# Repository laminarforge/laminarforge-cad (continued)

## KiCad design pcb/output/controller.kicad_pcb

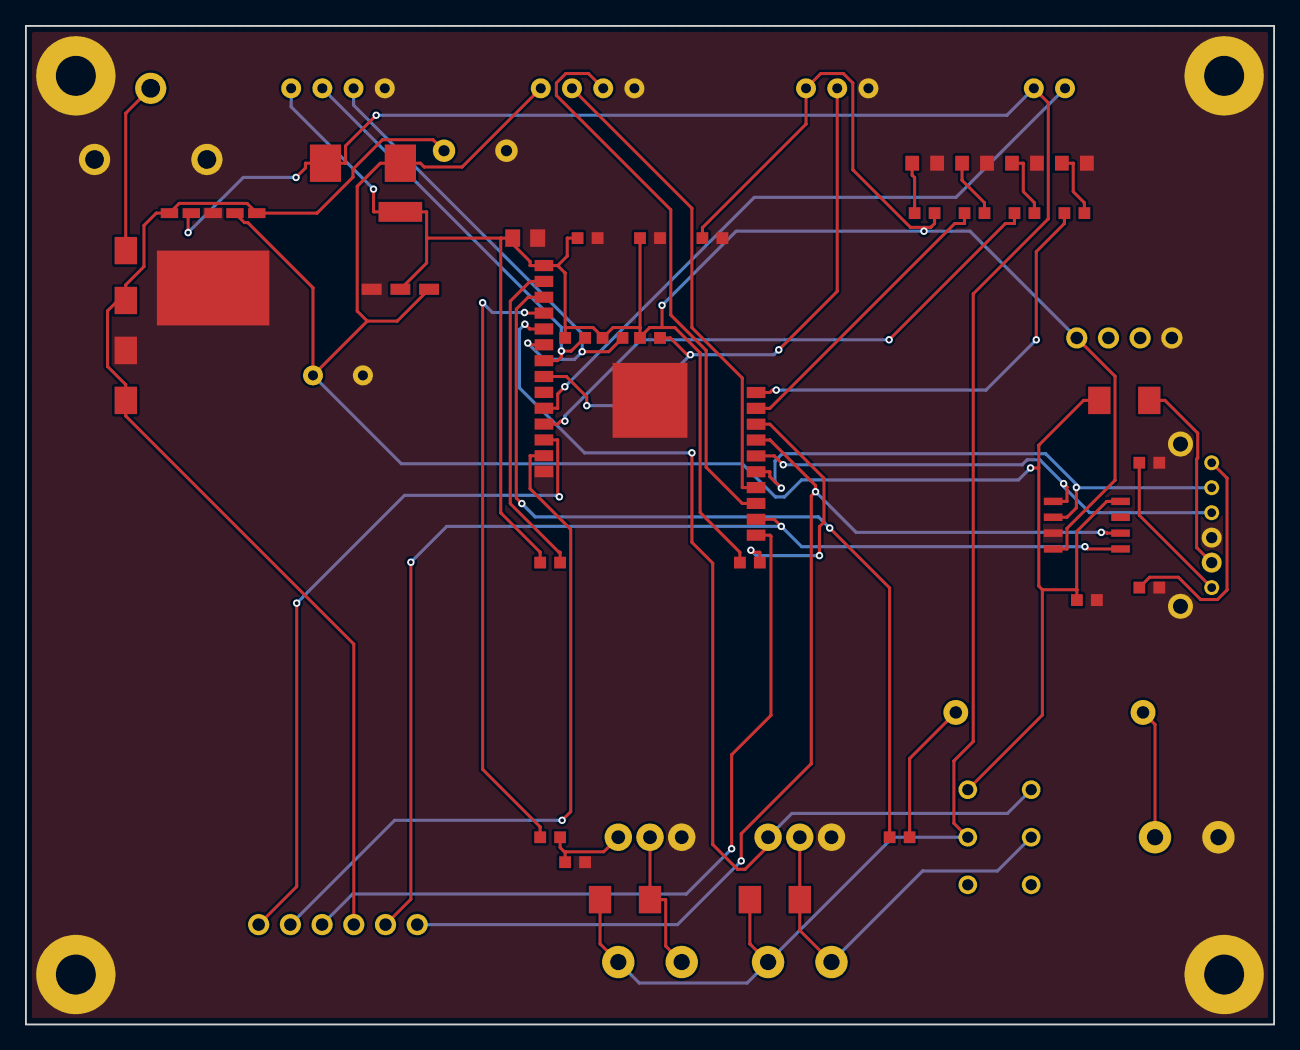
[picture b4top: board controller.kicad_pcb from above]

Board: 2 copper layers, 100.0 x 80.0 mm, 54 parts (0 on the bottom side), 39 nets.

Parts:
C1: 220uF_35V; CP_Radial_D8.0mm
C2: 220uF_10V; CP_Radial_D6.3mm
C3, C4, C5, C7: 100nF; C_0603
C6: 10uF; C_0805
D1, D3, D4, D5: SS54; SMA
D2: SMBJ30A; SMB
H1, H2, H3, H4: MountingHole_3.2mm_M3
J1: DC_BARREL_2.1x5.5mm; BarrelJack_2.1x5.5mm
J2: KSD9700_100C_NC; ThermalCutoff_KSD9700
J3: ScrewTerm_SSR_Ctrl; ScrewTerm_2.54mm_2P
J4: ScrewTerm_Fan; ScrewTerm_2.54mm_2P
J5: ScrewTerm_Solenoid; ScrewTerm_2.54mm_2P
J6: JST_SHT40; JST_PH_4P
J7: JST_MHZ19; JST_PH_4P
J8: JST_DS18B20; JST_PH_3P
J9: JST_Window_Heater; JST_PH_2P
J10: USB-C_Receptacle; USB_C_Receptacle_HRO-TYPE-C-31-M-12
J11: TMC2209_Header; PinHeader_1x6_2.54mm
J12: SWD_Header; PinHeader_1x4_2.54mm
K1: G6K-2F-Y; Relay_DPDT_Omron_G6K
L1: 33uH_CDRH127; L_Wurth_WE-PD_7345
LD1: GREEN_LED; LED_0805
LD2: BLUE_LED; LED_0805
LD3: YELLOW_LED; LED_0805
LD4: RED_LED; LED_0805
Q1, Q2: IRLZ44N; TO-220-3_Vertical
R1, R2: 10K; R_0603
R3, R4, R5: 4.7K; R_0603
R6: 1K; R_0603
R7: 100R; R_0603
R8: 100K; R_0603
R9, R10, R11, R12: 330R; R_0603
R13, R14: 5.1K; R_0603
U1: ESP32-S3-WROOM-1-N8R8; ESP32-S3-WROOM-1
U2: LM2596S-5.0; TO-263-5
U3: AMS1117-3.3; SOT-223
U4: CH340N; SOP-8

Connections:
+3V3: C3.1, C4.1, C5.1, C6.1, J6.1, J8.1, J12.1, R1.1, R2.1, R3.1, R4.1, R5.1, R9.2, U1.2, U3.2, U3.TAB, U4.4
+5V: C2.1, C7.1, D5.1, J7.1, K1.1, L1.2, U2.4, U3.3, U4.8
+12V: D3.1, D4.1, J4.1, J5.1, J9.1, K1.3, L1.1, U2.2
+24V_IN: D1.2, J1.1
+24V_SW: C1.1, D1.1, D2.1, J11.4, U2.1, U2.5
CO2_SOL_OUT_N: D4.2, J5.2, K1.4, Q2.2
CO2_SOL_PWM: K1.2, Q2.1, U1.6
DIR: J11.2, U1.14
DS18B20_DATA: J8.2, R5.2, U1.9
EN_N: J11.3, U1.20
ESP_BOOT: R2.2, U1.27
ESP_EN: R1.2, U1.3
FAN_GATE: Q1.1, R7.2, R8.1
FAN_OUT_N: D3.2, J4.2, Q1.2
FAN_PWM: R7.1, U1.5
GND: C1.2, C2.2, C3.2, C4.2, C5.2, C6.2, C7.2, D2.2, H1.1, H2.1, H3.1, H4.1, J1.2, J1.3, J3.2, J6.4, J7.4, J8.3, J10.GND, J10.M1, J10.M2, J12.4, LD1.2, LD2.2, LD3.2, LD4.2, Q1.3, Q2.3, R8.2, R13.2, R14.2, U1.1, U1.15, U2.3, U2.TAB, U3.1, U4.3
HEATER_SSR_MCU: R6.1, U1.4
HEATER_SSR_OUT: J2.2, J3.1
HEATER_SSR_PRE: J2.1, R6.2
LED_FAULT: LD4.1, R12.2
LED_FAULT_DRV: R12.1, U1.29
LED_HEAT: LD3.1, R11.2
LED_HEAT_DRV: R11.1, U1.12
LED_PWR: LD1.1, R9.1
LED_WIFI: LD2.1, R10.2
LED_WIFI_DRV: R10.1, U1.28
MHZ19_RX: J7.3, U1.22
MHZ19_TX: J7.2, U1.23
SCL: J6.3, R4.2, U1.7
SDA: J6.2, R3.2, U1.8
STEP: J11.1, U1.13
TMC_UART_RX: J11.6, U1.26, U4.6
TMC_UART_TX: J11.5, U1.21, U4.5
USB_CC1: J10.CC1, R13.1
USB_CC2: J10.CC2, R14.1
USB_DN: J10.D-, U1.24, U4.2
USB_DP: J10.D+, U1.25, U4.1
VBUS: D5.2, J10.VBUS
WINDOW_HEATER: J9.2, U1.11

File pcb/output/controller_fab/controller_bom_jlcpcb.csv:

Reference,Value,LCSC,Footprint,Description
U1,ESP32-S3-WROOM-1-N8R8,C2913204,laminarforge:ESP32-S3-WROOM-1,WiFi/BT/BLE MCU module
U2,LM2596S-5.0,C9864,laminarforge:TO-263-5,Buck regulator 24V->5V 2A
U3,AMS1117-3.3,C6186,laminarforge:SOT-223,LDO 5V->3.3V 1A
U4,CH340N,C506813,laminarforge:SOP-8,USB-UART bridge
J1,DC_BARREL_2.1x5.5mm,C3296358,laminarforge:BarrelJack_2.1x5.5mm,24V DC input
D1,SS54,C22452,laminarforge:SMA,Schottky reverse-protection
D2,SMBJ30A,C8963,laminarforge:SMB,TVS 30V 600W
C1,220uF_35V,C92068,laminarforge:CP_Radial_D8.0mm,24V input bulk cap
C2,220uF_10V,C41238,laminarforge:CP_Radial_D6.3mm,5V rail bulk cap
L1,33uH_CDRH127,C1046,laminarforge:L_Wurth_WE-PD_7345,LM2596 output inductor
C3,100nF,C14663,laminarforge:C_0603,MCU decoupling
C4,100nF,C14663,laminarforge:C_0603,MCU decoupling
C5,100nF,C14663,laminarforge:C_0603,MCU decoupling
C6,10uF,C15850,laminarforge:C_0805,MCU bulk decoupling
C7,100nF,C14663,laminarforge:C_0603,CH340 VCC bypass
R1,10K,C25804,laminarforge:R_0603,EN pull-up
R2,10K,C25804,laminarforge:R_0603,BOOT pull-up
R3,4.7K,C23162,laminarforge:R_0603,SDA pull-up
R4,4.7K,C23162,laminarforge:R_0603,SCL pull-up
R5,4.7K,C23162,laminarforge:R_0603,1-Wire pull-up
R6,1K,C21190,laminarforge:R_0603,SSR control series
R7,100R,C22775,laminarforge:R_0603,Fan MOSFET gate resistor
R8,100K,C25741,laminarforge:R_0603,Fan MOSFET gate pulldown
R9,330R,C23138,laminarforge:R_0603,LED current-limit
R10,330R,C23138,laminarforge:R_0603,LED current-limit
R11,330R,C23138,laminarforge:R_0603,LED current-limit
R12,330R,C23138,laminarforge:R_0603,LED current-limit
LD1,GREEN_LED,C72041,laminarforge:LED_0805,Status LED
LD2,BLUE_LED,C72041,laminarforge:LED_0805,Status LED
LD3,YELLOW_LED,C72041,laminarforge:LED_0805,Status LED
LD4,RED_LED,C72041,laminarforge:LED_0805,Status LED
Q1,IRLZ44N,C69224,laminarforge:TO-220-3_Vertical,Fan MOSFET
D3,SS54,C22452,laminarforge:SMA,Fan flyback diode
Q2,IRLZ44N,C69224,laminarforge:TO-220-3_Vertical,CO2 solenoid MOSFET
D4,SS54,C22452,laminarforge:SMA,Solenoid flyback diode
K1,G6K-2F-Y,C37368,laminarforge:Relay_DPDT_Omron_G6K,5V EMR CO2 solenoid (alt path)
J2,KSD9700_100C_NC,C2909862,laminarforge:ThermalCutoff_KSD9700,Overtemp cutoff (SSR interlock)
J3,ScrewTerm_SSR_Ctrl,C8735,laminarforge:ScrewTerm_2.54mm_2P,SSR control output
J4,ScrewTerm_Fan,C8735,laminarforge:ScrewTerm_2.54mm_2P,12V fan output
J5,ScrewTerm_Solenoid,C8735,laminarforge:ScrewTerm_2.54mm_2P,5V CO2 solenoid output
J6,JST_SHT40,C131367,laminarforge:JST_PH_4P,SHT40 remote connector
J7,JST_MHZ19,C131367,laminarforge:JST_PH_4P,MH-Z19B remote connector
J8,JST_DS18B20,C131365,laminarforge:JST_PH_3P,DS18B20 remote connector
J9,JST_Window_Heater,C131366,laminarforge:JST_PH_2P,Window anti-condensation heater
J10,USB-C_Receptacle,C165948,laminarforge:USB_C_Receptacle_HRO-TYPE-C-31-M-12,USB-C programming port
J11,TMC2209_Header,C124378,laminarforge:PinHeader_1x6_2.54mm,TMC2209 stepper driver breakout
J12,SWD_Header,C124379,laminarforge:PinHeader_1x4_2.54mm,SWD/JTAG debug
R13,5.1K,C23186,laminarforge:R_0603,USB-C CC1 pulldown
R14,5.1K,C23186,laminarforge:R_0603,USB-C CC2 pulldown
D5,SS54,C22452,laminarforge:SMA,VBUS->5V OR-ing schottky

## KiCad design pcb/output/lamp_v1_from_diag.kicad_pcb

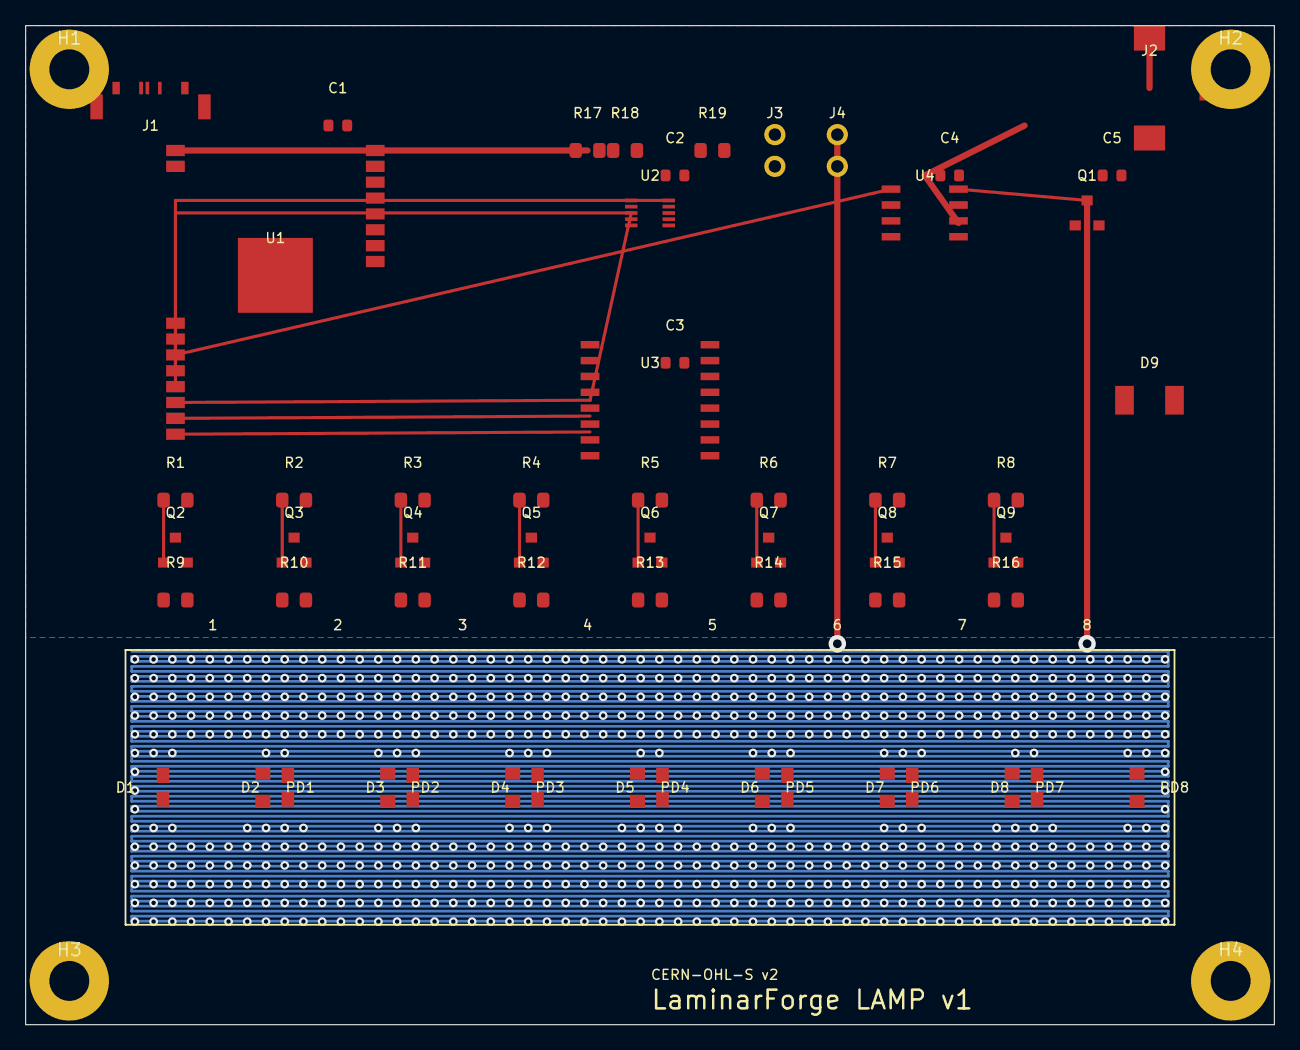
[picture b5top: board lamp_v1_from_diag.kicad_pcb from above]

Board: 2 copper layers, 100.0 x 80.0 mm, 62 parts (0 on the bottom side), 41 nets.

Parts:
C1, C2, C3, C4, C5: 100nF; C_0603
D1, D2, D3, D4, D5, D6, D7, D8: Blue_LED_460nm; LED_0805
D9: SS34; D_SMA
H1, H2, H3, H4: MountingHole_3.2mm_M3
J1: USB-C; USB_C_Receptacle
J2: DC_5525; BarrelJack_SMD
J3: NTC_CONN; PinHeader_1x02
J4: THERMAL_BREAK; PinHeader_1x02
PD1, PD2, PD3, PD4, PD5, PD6, PD7, PD8: VEMD5510C
Q1: AO3400A; SOT-23
Q2, Q3, Q4, Q5, Q6, Q7, Q8, Q9: MMBT3904; SOT-23
R1, R2, R3, R4, R5, R6, R7, R8: 1K; R_0805
R9, R10, R11, R12, R13, R14, R15, R16: 100R; R_0805
R17, R18: 4.7K; R_0805
R19: 10K; R_0805
U1: ESP32-S3-WROOM-1-N8; ESP32-S3-WROOM-1
U2: ADS1115IDGSR; MSOP-10
U3: CD74HC4051M; SOIC-16W
U4: TC4427ACOA713; SOIC-8

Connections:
+3V3: C1.1, C2.1, C3.1, C4.1, C5.1, R17.1, R18.1, R19.1, U1.2, U1.3, U2.8, U3.16
+5V: R9.1, R10.1, R11.1, R12.1, R13.1, R14.1, R15.1, R16.1, U4.6
+12V: D9.2, J2.1, J4.1
ADC_AIN1: J3.1, R19.2, U2.5
GND: C1.2, C2.2, C3.2, C4.2, C5.2, D1.2, D2.2, D3.2, D4.2, D5.2, D6.2, D7.2, D8.2, H1.1, H2.1, H3.1, H4.1, J1.A1, J1.A12, J1.S1, J1.S2, J2.2, J2.3, J3.2, PD1.2, PD2.2, PD3.2, PD4.2, PD5.2, PD6.2, PD7.2, PD8.2, Q1.2, Q2.2, Q3.2, Q4.2, Q5.2, Q6.2, Q7.2, Q8.2, Q9.2, R1.2, R2.2, R3.2, R4.2, R5.2, R6.2, R7.2, R8.2, U1.GND, U2.1, U2.3, U3.6, U3.7, U3.8, U4.2, U4.3, U4.4
HEATER_PWM: U1.15, U4.1
LED_BASE: R1.1, R2.1, R3.1, R4.1, R5.1, R6.1, R7.1, R8.1
LED_BASE_0: Q2.1, U1.21
LED_BASE_1: Q3.1, U1.22
LED_BASE_2: Q4.1, U1.23
LED_BASE_3: Q5.1, U1.24
LED_BASE_4: Q6.1, U1.25
LED_BASE_5: Q7.1, U1.26
LED_BASE_6: Q8.1, U1.27
LED_BASE_7: Q9.1, U1.28
LED_COL: R9.2, R10.2, R11.2, R12.2, R13.2, R14.2, R15.2, R16.2
LED_COL_0: D1.1, Q2.3
LED_COL_1: D2.1, Q3.3
LED_COL_2: D3.1, Q4.3
LED_COL_3: D4.1, Q5.3
LED_COL_4: D5.1, Q6.3
LED_COL_5: D6.1, Q7.3
LED_COL_6: D7.1, Q8.3
LED_COL_7: D8.1, Q9.3
MOSFET_DRAIN: D9.1, Q1.3
MOSFET_GATE: Q1.1, U4.7
MUX_S0: U1.18, U3.11
MUX_S1: U1.19, U3.10
MUX_S2: U1.20, U3.9
MUX_Y0: PD1.1, U3.13
MUX_Y1: PD2.1, U3.14
MUX_Y2: PD3.1, U3.15
MUX_Y3: PD4.1, U3.12
MUX_Y4: PD5.1, U3.1
MUX_Y5: PD6.1, U3.5
MUX_Y6: PD7.1, U3.2
MUX_Y7: PD8.1, U3.4
SCL: R18.2, U1.17, U2.10
SDA: R17.2, U1.16, U2.9
USB_DN: J1.A7, U1.14
USB_DP: J1.A6, U1.13

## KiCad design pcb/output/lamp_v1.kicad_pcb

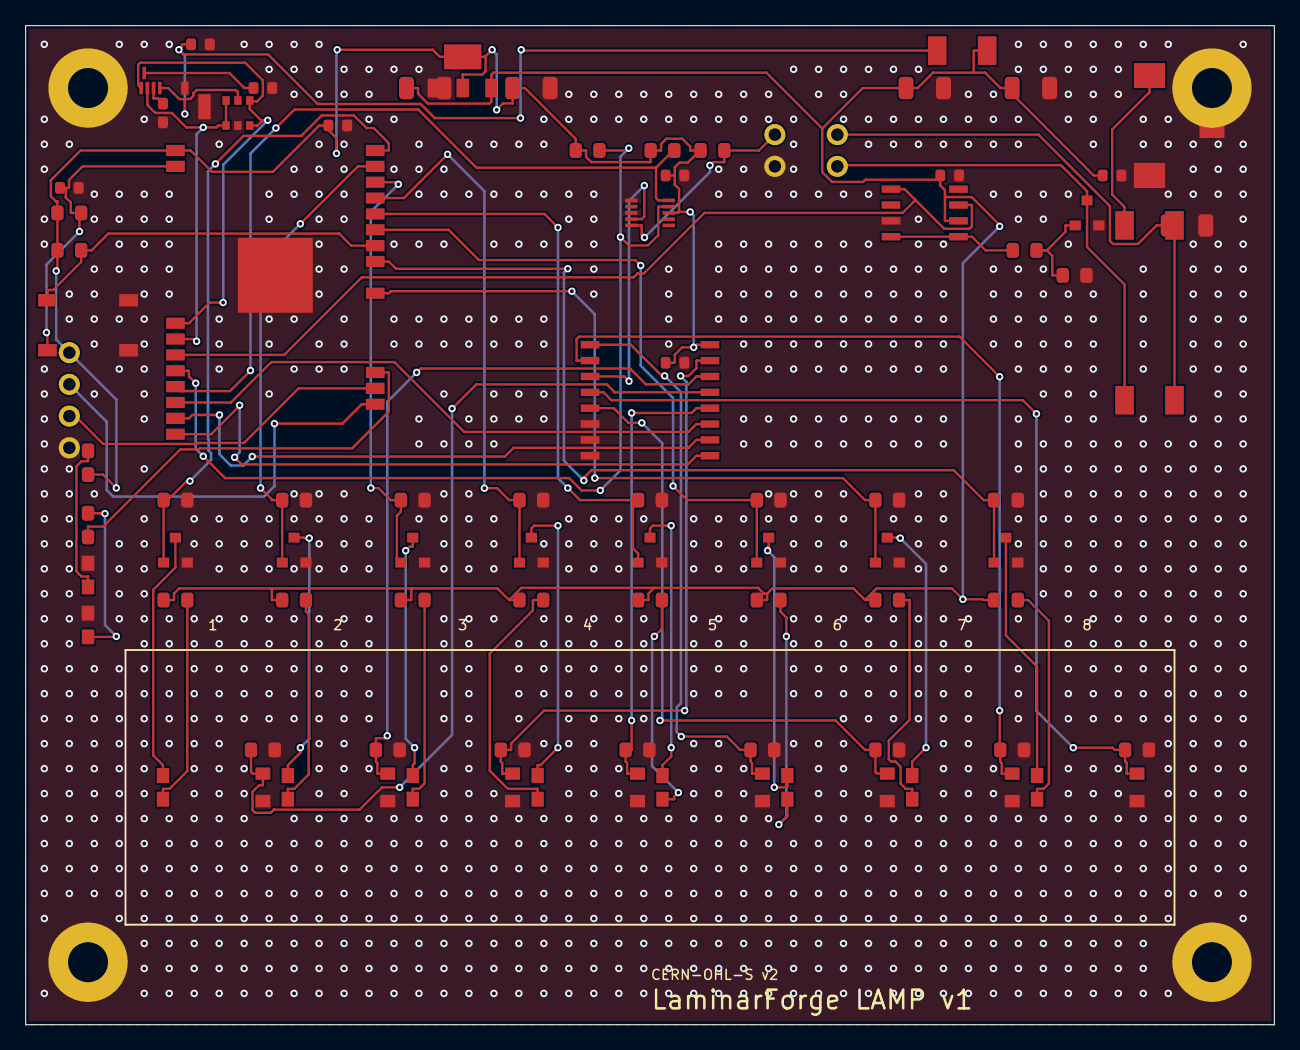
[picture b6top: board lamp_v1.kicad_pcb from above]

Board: 2 copper layers, 100.0 x 80.0 mm, 94 parts (0 on the bottom side), 60 nets.

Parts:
C1, C2, C3, C4, C5: 100nF; C_0603
C6, C7, C8, C9, C10: 22uF; C_1206
C11, C12: 1uF; C_0603
D1, D2, D3, D4, D5, D6, D7, D8: Blue_LED_460nm; LED_0805
D9, D10, D14: SS34; D_SMA
D11: Green_LED; LED_0805_STATUS
D12: Blue_LED; LED_0805_STATUS
H1, H2, H3, H4: MountingHole_3.2mm_M3
J1: USB-C; USB_C_Receptacle
J2: DC_5525; BarrelJack_SMD
J3: NTC_CONN; PinHeader_1x02
J4: HEATER_CONN; PinHeader_1x02
J5: UART_HDR; PinHeader_1x04
PD1, PD2, PD3, PD4, PD5, PD6, PD7, PD8: VEMD5510C
Q1: AO3400A; SOT-23
Q2, Q3, Q4, Q5, Q6, Q7, Q8, Q9: MMBT3904; SOT-23
R1, R2, R3, R4, R5, R6, R7, R8, R32, R33: 1K; R_0805
R9, R10, R11, R12, R13, R14, R15, R16, R34: 100R; R_0805
R17, R18: 4.7K; R_0805
R19, R28, R29, R35: 10K; R_0805
R20, R21, R22, R23, R24, R25, R26, R27: 100K; R_0805
R30, R31: 5.1K; R_0603
SW1: BOOT; SW_Tactile_6mm
SW2: RESET; SW_Tactile_6mm
U1: ESP32-S3-WROOM-1-N8; ESP32-S3-WROOM-1
U2: ADS1115IDGSR; MSOP-10
U3: CD74HC4051M; SOIC-16W
U4: TC4427ACOA713; SOIC-8
U6: AMS1117-3.3; SOT-223
U7: USBLC6-2SC6; SOT-23-6

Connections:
+3V3: C1.1, C2.1, C3.1, C9.1, J5.1, R17.1, R18.1, R19.1, R28.1, R29.1, R32.1, U1.2, U2.8, U3.16, U6.2, U6.4
+5V: C4.1, C5.1, C6.1, C7.1, C8.1, D14.2, R9.1, R10.1, R11.1, R12.1, R13.1, R14.1, R15.1, R16.1, U4.6, U6.3
+12V: C10.1, D9.2, D10.2, J4.1
+12V_RAW: D10.1, J2.1
ADC_AIN1: J3.1, R19.2, U2.5
ESP_EN: C11.1, R28.2, SW2.1, U1.3
ESP_GPIO0: R29.2, SW1.1, U1.27
ESP_GPIO_ACT: R33.1, U1.35
GATE_DRV: R34.1, U4.4, U4.5
GND: C1.2, C2.2, C3.2, C4.2, C5.2, C6.2, C7.2, C8.2, C9.2, C10.2, C11.2, C12.2, D11.2, D12.2, H1.1, H2.1, H3.1, H4.1, J1.A1, J1.A12, J1.S1, J1.S2, J2.2, J2.3, J3.2, J5.4, PD1.2, PD2.2, PD3.2, PD4.2, PD5.2, PD6.2, PD7.2, PD8.2, Q1.2, Q2.2, Q3.2, Q4.2, Q5.2, Q6.2, Q7.2, Q8.2, Q9.2, R1.2, R2.2, R3.2, R4.2, R5.2, R6.2, R7.2, R8.2, R20.2, R21.2, R22.2, R23.2, R24.2, R25.2, R26.2, R27.2, R30.2, R31.2, R35.2, SW1.2, SW2.2, U1.GND, U2.1, U2.3, U3.6, U3.7, U3.8, U4.3, U6.1, U7.2
HEATER_P: D9.1, J4.2, Q1.3
HEATER_PWM: U1.15, U4.1, U4.7
LED_ACT_ANODE: D12.1, R33.2
LED_BASE_0: Q2.1, R1.1, U1.21
LED_BASE_1: Q3.1, R2.1, U1.22
LED_BASE_2: Q4.1, R3.1, U1.23
LED_BASE_3: Q5.1, R4.1, U1.24
LED_BASE_4: Q6.1, R5.1, U1.25
LED_BASE_5: Q7.1, R6.1, U1.26
LED_BASE_6: Q8.1, R7.1, U1.30
LED_BASE_7: Q9.1, R8.1, U1.28
LED_CATH_0: D1.2, Q2.3
LED_CATH_1: D2.2, Q3.3
LED_CATH_2: D3.2, Q4.3
LED_CATH_3: D4.2, Q5.3
LED_CATH_4: D5.2, Q6.3
LED_CATH_5: D6.2, Q7.3
LED_CATH_6: D7.2, Q8.3
LED_CATH_7: D8.2, Q9.3
LED_COL_0: D1.1, R9.2
LED_COL_1: D2.1, R10.2
LED_COL_2: D3.1, R11.2
LED_COL_3: D4.1, R12.2
LED_COL_4: D5.1, R13.2
LED_COL_5: D6.1, R14.2
LED_COL_6: D7.1, R15.2
LED_COL_7: D8.1, R16.2
LED_PWR_ANODE: D11.1, R32.2
MOSFET_GATE: Q1.1, R34.2, R35.1
MUX_COM: U2.4, U3.3
MUX_S0: U1.18, U3.11
MUX_S1: U1.19, U3.10
MUX_S2: U1.20, U3.9
MUX_Y0: PD1.1, R20.1, U3.13
MUX_Y1: PD2.1, R21.1, U3.14
MUX_Y2: PD3.1, R22.1, U3.15
MUX_Y3: PD4.1, R23.1, U3.12
MUX_Y4: PD5.1, R24.1, U3.1
MUX_Y5: PD6.1, R25.1, U3.5
MUX_Y6: PD7.1, R26.1, U3.2
MUX_Y7: PD8.1, R27.1, U3.4
SCL: R18.2, U1.17, U2.10
SDA: R17.2, U1.16, U2.9
UART_RX: J5.3, U1.36
UART_TX: J5.2, U1.37
USB_CC1: J1.A5, R30.1
USB_CC2: J1.B5, R31.1
USB_DN: J1.A7, U1.13, U7.3, U7.4
USB_DP: J1.A6, U1.14, U7.1, U7.6
VBUS: C12.1, D14.1, J1.A4, U7.5

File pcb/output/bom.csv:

Comment,Designator,Footprint,LCSC Part Number
"100K","R20,R21,R22,R23,R24,R25,R26,R27","R_0805","C17407"
"100R","R9,R10,R11,R12,R13,R14,R15,R16,R34","R_0805","C17408"
"100nF","C1,C2,C3,C4,C5","C_0603","C14663"
"10K","R19,R28,R29,R35","R_0805","C17414"
"1K","R1,R2,R3,R4,R5,R6,R7,R8,R32,R33","R_0805","C17513"
"1uF","C11,C12","C_0603","C15849"
"22uF","C6,C7,C8,C9,C10","C_1206","C5672"
"4.7K","R17,R18","R_0805","C17673"
"5.1K","R30,R31","R_0603","C25905"
"ADS1115IDGSR","U2","MSOP-10","C37593"
"AMS1117-3.3","U6","SOT-223","C6186"
"AO3400A","Q1","SOT-23","C20917"
"BOOT","SW1","SW_Tactile_6mm","C318884"
"Blue_LED","D12","LED_0805_STATUS","C2286"
"Blue_LED_460nm","D1,D2,D3,D4,D5,D6,D7,D8","LED_0805","C2286"
"CD74HC4051M","U3","SOIC-16W","C139301"
"DC_5525","J2","BarrelJack_SMD","C381116"
"ESP32-S3-WROOM-1-N8","U1","ESP32-S3-WROOM-1","C2913198"
"Green_LED","D11","LED_0805_STATUS","C2297"
"MMBT3904","Q2,Q3,Q4,Q5,Q6,Q7,Q8,Q9","SOT-23","C20526"
"RESET","SW2","SW_Tactile_6mm","C318884"
"SS34","D9,D10,D14","D_SMA","C8678"
"TC4427ACOA713","U4","SOIC-8","C636886"
"USB-C","J1","USB_C_Receptacle","C168688"
"USBLC6-2SC6","U7","SOT-23-6","C7519"
"VEMD5510C","PD1,PD2,PD3,PD4,PD5,PD6,PD7,PD8","VEMD5510C","C2526474"

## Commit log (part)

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2026-05-12 Add LAMP Rev A mechanical access gate
2026-05-12 Add LAMP Rev A assembly inspection gate
2026-05-13 Add LAMP Rev A assembly fixture readability gate
2026-05-13 Expose LAMP Rev A board to CAD viewer output
2026-05-26 Add cell culture starter equipment plan
2026-05-27 Gate CO2 incubator publication on research validation
2026-05-27 Verify CO2 incubator CAD against research gates
2026-05-27 Expand cell culture equipment design matrix
2026-05-27 Add starter equipment verifier and support CAD
2026-05-27 Add aspirator waste trap holder CAD
2026-05-27 Add chip priming tubing fixture CAD
2026-05-27 Break down cell culture equipment readiness boundaries
2026-05-27 Add water bath safety kit CAD
2026-05-27 Make liquid handling plan automation-first
2026-05-27 Add automated media exchange cassette CAD
2026-05-27 Add sterile tubing harness CAD
2026-05-27 Add cassette bench nest CAD
2026-05-27 Document multimodal culture monitoring design
2026-05-27 Document tissue chip reproducibility controls
2026-05-27 Add sealed culture module CAD
2026-05-27 Add automated seeding coating station CAD module
2026-05-27 Add automated culture workflow CAD modules
2026-05-27 Add closed culture automation support modules
2026-05-27 Add cassette transfer and position control CAD modules
2026-05-27 Add closed upstream automation CAD modules
2026-05-27 Add deviation and release QC CAD modules
2026-05-27 Add support utility cell culture CAD modules
2026-05-27 Add closed consumable QC CAD modules
2026-05-27 Add fluid QC and custody CAD modules
2026-05-27 Add measurement QC CAD modules
2026-05-27 Add environmental utility validation CAD modules
2026-05-27 Add closed utility validation CAD modules
2026-05-27 Add robot collision force limit validation station
2026-05-27 Add closed airlock pressure decay interlock challenge station
2026-05-27 Add cassette barcode RFID reconciliation station
2026-05-27 Add cold-chain excursion unpack station CAD generator
2026-05-27 Add closed perfusion drainability CAD station
2026-05-27 Add disinfectant contact-time CAD station
2026-05-27 Add reagent bag pressure hold creep station
2026-05-27 Add incubator condensate cross-contamination witness station
2026-05-27 Add reservoir cap septum leak life station
2026-05-27 Add incubator fan flow shadowing station
2026-05-27 Add light exposure witness validation station
2026-05-27 Add closed cassette shipping vibration logger dock station
2026-05-27 Add sensor probe cleanability residue station
2026-05-27 Add VHP residue aeration witness station
2026-05-27 Add closed media bag rocking shear surrogate station
2026-05-27 Add closed oxygen MFC blend calibration station CAD generator
2026-05-27 Add cassette seed fluorescent uniformity station
2026-05-27 Add closed pass-through handoff repeatability CAD generator
2026-05-27 Add media analyte calibration custody station
2026-05-27 Add condensate drain trap cleanability station
2026-05-27 Add closed cell harvest neutralization timing station
2026-05-27 Add closed ECM coating reagent thaw dwell station
2026-05-27 Add closed cassette fixation rinse custody station
2026-05-27 Add closed myco sterility custody split station generator
2026-05-27 Add closed iPSC media-change recipe verification station
2026-05-27 Add closed waste-line interlock validation station CAD generator
2026-05-27 Add closed cassette evaporation osmotic drift sentinel station
2026-05-27 Add closed pump calibration station CAD generator
2026-05-27 Add closed media degassing priming station CAD generator
2026-05-27 Add closed airlock gasket leak witness station
2026-05-27 Add closed media reservoir thermal validation station CAD generator
2026-05-27 Add closed cassette media exchange washout station CAD generator
2026-05-27 Add closed incubator power failure holdover witness station
2026-05-27 Add closed connector cap-loss prevention station CAD generator
2026-05-27 Add closed reagent thaw bubble wetness station
2026-05-27 Add rack slot identity load history station CAD generator
2026-05-27 Add cassette orientation error station CAD generator
2026-05-27 Add airflow shadow smoke witness station CAD generator
2026-05-27 Add waste vent filter breakthrough CAD station
2026-05-27 Add cassette barrier breach dye trace station
2026-05-27 Add closed validation CAD batch 13 modules
2026-05-27 Add closed passage lot chain identity station
2026-05-27 Add closed cleaning residual TOC conductivity release station
2026-05-27 Add closed validation CAD batch 14 modules
2026-05-27 Add chip lane pressure relief burst guard CAD station
2026-05-27 Add closed cell settling time mixing hold station
2026-05-27 Add connector mate/demate force trace station CAD bin
2026-05-27 Add closed media bag scale drift false mass station
2026-05-27 Add flow split symmetry station CAD bin
2026-05-27 Add closed reagent lot barcode scale station
2026-05-27 Add closed validation CAD batch 15 modules
2026-05-27 Add gasket install torque compression station
2026-05-27 Add cleanroom pressure cascade smoke recovery station
2026-05-27 Add closed cassette edge-center rebalance station
2026-05-27 Add perfusion alarm quarantine diverter CAD station
2026-05-27 Add feed harvest bag lot mixup prevention station
2026-05-27 Add closed validation CAD batch 16 modules
2026-05-27 Add sensor clock drift resync challenge station
2026-05-27 Add closed feed harvest line reversal validation station
2026-05-27 Add alarm false positive fault injection CAD station
2026-05-27 Add positive pressure gowning reentry station
2026-05-27 Add sensor packet loss buffering challenge station
2026-05-27 Add incubator slot evaporation balance station
2026-05-27 Add clean-zone personnel material flow interlock CAD
2026-05-27 Add alarm escalation hold release station
2026-05-27 Add sensor stream replay audit trail station
2026-05-27 Add closed validation CAD batch 17 modules
2026-05-27 Add closed media gas equilibration hold loop station
2026-05-27 Add closed cell seeding homogeneity station
2026-05-27 Add closed cassette seeding angle dwell CAD station
2026-05-27 Add incubator humidity water quality sentinel CAD station
2026-05-27 Add closed validation CAD batch 18 modules
2026-05-27 Add closed cleanroom recovery validation station
2026-05-27 Add closed validation CAD batch 19 modules
2026-05-27 Add CO2 O2 gas changeover recovery station
2026-05-27 Add closed robotic media bag spike prime station
2026-05-27 Add closed microplate adapter station CAD
2026-05-27 Add thermal contact preload uniformity CAD station
2026-05-27 Add closed cell wash concentrate recovery CAD station
2026-05-27 Add closed perfusion bubble trap alarm station
2026-05-27 Add closed validation CAD batch 20 modules
2026-05-27 Add closed media hold-loop RTD tracer station
2026-05-27 Add cleanroom airflow smoke quantification CAD station
2026-05-27 Add cap torque seal integrity CAD station
2026-05-27 Add perfusion sensor crosstalk station
2026-05-27 Add media bag temp ramp fault station CAD
2026-05-27 Add humidity condensate drain clog overflow fault station
2026-05-27 Add closed cell lot hold-time tracer station CAD
2026-05-27 Add closed perfusion media viscosity pressure alarm station
2026-05-27 Add closed validation CAD batch 21 modules
2026-05-27 Add microfluidic lane occlusion pressure signature station
2026-05-27 Add cell attachment settle uniformity witness station
2026-05-27 Add fluid path lot release pressure flow station
2026-05-27 Add ECM dwell gelation validation station
2026-05-27 Add media exchange carryover shear validation station
2026-05-27 Add closed validation CAD batch 22 modules
2026-05-27 Add thaw-to-seed handoff validation station
2026-05-27 Add environmental probe shadow strain validation station
2026-05-27 Add airlock gasket wear particle shedding station
2026-05-27 Add closed validation CAD batch 23 modules
2026-05-27 Add decon residue false-clearance station
2026-05-27 Add startup shear ramp validation station CAD
2026-05-27 Add closed degas wetout leak station CAD
2026-05-27 Add cassette module pressure equalization station
2026-05-27 Add abort safe-state culture fixture CAD generator
2026-05-27 Add closed validation CAD batch 24 modules
2026-05-27 Add cassette barcode image focus occlusion station
2026-05-27 Add closed incubator gas recovery station
2026-05-27 Add flow sensor drift voting station CAD
2026-05-27 Add perfusion alarm evidence bundle station
2026-05-27 Add culture media deadleg flush station CAD
2026-05-27 Add closed perfusion temperature mismatch interlock station
2026-05-27 Add sterile air purge duration validation station
2026-05-27 Add condensate drain alarm recovery station CAD
2026-05-27 Add microdose recovery gravimetric station CAD
2026-05-27 Integrate closed validation CAD batch 25
    Register ten closed cell-culture validation stations in the equipment manifest and verifier.
    Add design-matrix and reproducibility-control notes for Batch25 validation modules.
    Drop generated STL blobs accidentally staged by worker branches and fix the sampling-bag deadleg datum sentinel geometry.
2026-05-27 Add closed media bag pooling interlock CAD station
2026-05-27 Add waste port misroute witness station CAD
2026-05-27 Add incubator airflow filter loading recovery CAD station
2026-05-27 Add backpressure waveform signature CAD station
2026-05-27 Add seed density gradient settle witness CAD station
2026-05-27 Add recirculation dead-zone tracer CAD station
2026-05-27 Integrate closed validation CAD batch 26
2026-05-27 Add incubator gas sampling condensate trap validation station
2026-05-27 Add cell-source bag agitation shear threshold station
2026-05-27 Add serpentine dye-front uniformity CAD station
2026-05-27 Add media additive precipitation filter blockage station
2026-05-27 Add closed incubator slot reassignment balance station
2026-05-27 Integrate closed validation CAD batch 27
2026-05-27 Add humidity reservoir slosh response CAD station
2026-05-27 Add dissolved gas bubble nucleation CAD station
2026-05-27 Add dissolved oxygen response lag mapping station
2026-05-27 Add autoclave cycle custody station CAD generator
2026-05-27 Integrate closed validation CAD batch 28
2026-05-27 Add closed perfusion media temperature step response CAD station
2026-05-27 Add evaporation edge guard media overlay station
2026-05-27 Add closed barcode RFID fogging readability station
2026-05-27 Add closed TEER electrode recovery CAD station
2026-05-27 Add ECM coating thickness uniformity witness station
2026-05-27 Add microfluidic chip lot metrology fit CAD station
2026-05-27 Integrate closed validation CAD batch 29
2026-05-27 Add waste line contamination sentinel CAD generator
2026-05-27 Add closed seed density inline mix validation CAD
2026-05-27 Add material debag static particle burst CAD station
2026-05-27 Add live dead viability crosscheck CAD station
2026-05-27 Add clump filter viability sentinel CAD station
2026-05-27 Add preseed air bubble quarantine CAD station
2026-05-27 Add media bag false mass sentinel CAD generator
2026-05-28 Add cassette incubator manufacturing readiness package
2026-05-28 Add sealed microfluidic cartridge CAD coupons
2026-05-29 Add 16-slot cassette incubator first article CAD
2026-05-29 Fix LaminarForge CAD CI lint gate
2026-05-29 Integrate recovered LaminarForge CAD stations
2026-05-31 Redesign LAMP CAD around sealed cartridge
2026-06-04 Document 16-slot cassette first-build baseline
2026-06-04 Add 16-slot cassette A0 interface spec
2026-06-04 Add A2 lid clamp subsystem spec
2026-06-04 Add A1 carrier subsystem spec
2026-06-04 Add A3 gasket subsystem spec
2026-06-04 Add 16-slot cassette A4 DFM spec
2026-06-04 Integrate 16-slot cassette mechanical stack v0
2026-06-04 Add 16-slot cassette A7 validation fixture spec
2026-06-04 Add 16-slot cassette A8 build package
2026-06-04 Add 16-slot cassette A9 STEP drawing plan
2026-06-04 Add 16-slot cassette STEP exporter
2026-06-04 Add 16-slot cassette print coupons
2026-06-04 Anchor print coupon raised features
2026-06-04 Define standard-footprint AAV condition module architecture
2026-06-04 Clarify 16-zone AAV module scale target
2026-06-04 Add single AAV condition module mockup
2026-06-05 Reduce connector coupon print warping
2026-06-05 Add Rev A connector gasket insert
